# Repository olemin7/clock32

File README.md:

# dependency
git clone git@github.com:olemin7/esp32_idf_libs.git libs
# Troubleshooting

* Program upload failure

    * Hardware connection is not correct: run `idf.py -p PORT monitor`, and reboot your board to see if there are any output logs.
    * The baud rate for downloading is too high: lower your baud rate in the `menuconfig` menu, and try again.

https://esp-idf-lib.readthedocs.io/en/latest/groups/bmp180.html

https://github.com/espressif/esp-iot-solution

# esp32c3_supermini
    Pin     | ADC | func |
GPIO_NUM_0  | A0  |      |photoresistor
GPIO_NUM_1  | A1  |      |
GPIO_NUM_2  | A2  |      |
GPIO_NUM_3  | A3  |      |
GPIO_NUM_4  | A4  | SCK  | max7219 CLK
3V3
GND
5V
-------------------------------------
GPIO_NUM_5  | A5  | MISO | max7219 CS
GPIO_NUM_6  |     | MOSI | max7219 DIN
GPIO_NUM_7  |     | SS   | 
GPIO_NUM_8  |     | SDA  | LED           |HTU2x SDA
GPIO_NUM_9  |     | SDL  | BOOT_BUTTON   |HTU2x SDL
GPIO_NUM_10 |     |      |
GPIO_NUM_20 |     | RX   |
GPIO_NUM_21 |     | TX   |

# Display MAX7219 

https://github.com/DiegoPaezA/ESP32-freeRTOS/blob/master/i2c_scanner/main/i2c_scanner.c
https://github.com/espressif/esp-iot-solution/tree/dd15770d0f8c5fedea78809737f04b63d3765c83/examples/sensors/sensor_hub_monitor

# build CLI
. ~/esp/v5.5.1/esp-idf/export.sh
# path to esp32_idf_libs, relative to project root (used by main/Kconfig.projbuild)
# default: copy fetched by CMake FetchContent
export MY_ESP_LIBRARIES_PATH=/build/_deps/my_idf_libs-src
# to work on a local checkout of the libs instead (path is still appended to project root):
# export MY_ESP_LIBRARIES_LOCAL=1
idf.py set-target esp32c3
idf.py build
idf.py menuconfig
idf.py -p /dev/ttyACM0 flash

null in the env https://github.com/espressif/idf-eclipse-plugin/issues/535https://components.espressif.com/

Check the values in your sdkconfig for LOG_MAXIMUM_LEVEL. It defaults to matching LOG_DEFAULT_LEVEL which limits what values you can use by default.

# mqtt test
sudo apt-get install mosquitto mosquitto-clients

sudo vim /etc/mosquitto/mosquitto.conf 
add
  listener 1883 0.0.0.0
  allow_anonymous true

sudo ufw allow 1883

sudo /etc/init.d/mosquitto restart

mosquitto_sub -h nas.local -d -t advertisement
mosquitto_pub -h nas.local -d -t cmd -m "adv"

one terminal
mosquitto_sub -d -t hello/world
mosquitto_sub -d -t stat/weather -h central.local
Connect to another ssh session and run
mosquitto_pub -d -t hello/world -m "Hello from terminal window 2!"

sudo tail -f /var/log/mosquitto/mosquitto.log

mosquitto_sub -h nas.local -d -t '#'
https://github.com/nopnop2002/esp-idf-json/tree/master/json-basic-object

[rtc]
CONFIG_RTC_CLK_SRC ->External 32kHz crystal

[sntp]
Request interval to update time
CONFIG_TIMEZONE "GMT-2"
https://github.com/nayarsystems/posix_tz_db/blob/master/zones.csv
EET-2EEST,M3.5.0/3,M10.5.0/4

[button]
todo boot btn to go provision mode?

[termomenter]
https://www.lucadentella.it/en/2017/10/13/esp32-24-i2c-un-esempio-pratico-con-sensore-htu21d/
https://github.com/kimsniper/htu21d/tree/master/examples/esp32_implementation/main
si7021 (htu2x)

[esp-idf-lib]
https://esp-idf-lib.readthedocs.io/en/latest/index.html
git clone git@github.com:UncleRus/esp-idf-lib.git

[adc]
https://docs.espressif.com/projects/esp-idf/en/v4.4.8/esp32/api-reference/peripherals/adc.html
#photoresistor (GND ) -photoresistor- (A0) -resistor 10k- (+3.3)

https://esp32tutorials.com/esp32-esp-idf-max7219-dot-matrix-display

https://xantorohara.github.io/led-matrix-editor/#7e1818181c181800|7e060c3060663c00|3c66603860663c00|30307e3234383000|3c6660603e067e00|3c66663e06663c00|1818183030667e00|3c66663c66663c00|3c66607c66663c00|3c66666e76663c00

[json]
https://github.com/nopnop2002/esp-idf-json
# cmd list
export TARGET_MAC=64E833885558
export TARGET_MAC=64E833880880
export TARGET_MAC=64E83387D7D0
export TARGET_MAC=64E8338811DC
export TARGET_MAC=64E833882354
export MOSQUITO_ADDR=192.168.1.2
mosquitto_sub -d -t response/$TARGET_MAC -h $MOSQUITO_ADDR
mosquitto_sub -d -t devices/$TARGET_MAC/# -h $MOSQUITO_ADDR

mosquitto_pub -d -t cmd/$TARGET_MAC -h $MOSQUITO_ADDR -m '{"cmd":"help"}' 
mosquitto_pub -d -t cmd/$TARGET_MAC -h $MOSQUITO_ADDR -m '{"cmd":"version"}' 
mosquitto_pub -d -t cmd/$TARGET_MAC -h $MOSQUITO_ADDR -m '{"cmd":"svitlobot","payload":{"enabled":true,"interval_s":120}}' 
mosquitto_pub -d -t cmd/$TARGET_MAC -h $MOSQUITO_ADDR -m '{"cmd":"config"}' 

mosquitto_pub -d -t cmd/$TARGET_MAC -m '{"cmd":"ldr","payload":{"min":100,"max":3000}}' -h nas.local
mosquitto_pub -d -t cmd/$TARGET_MAC -m '{"cmd":"restart"}' -h $MOSQUITO_ADDR

mosquitto_pub -d -t cmd/$TARGET_MAC -m '{"cmd":"brightness","payload":{"points":[{"lighting":1530,"brightness":10}]}}' -h nas.local

mosquitto_pub -d -t cmd/$TARGET_MAC -h  $MOSQUITO_ADDR -m '{"cmd":"brightness","payload":{"points":[{"lighting":1530,"brightness":10}]}}' 

mosquitto_pub -d -t cmd/$TARGET_MAC -h $MOSQUITO_ADDR -m '{"cmd":"display"}'

{"cmd":"display","payload":{"segment_rotation":0,"segment_upsidedown":false,"mirrored":false}}

'{"cmd":"display","payload":{"segment_rotation":3,"segment_upsidedown":true,"mirrored":true}}
64E833885558 '{"cmd":"display","payload":{"segment_rotation":1,"segment_upsidedown":true,"mirrored":true}}'

'{"cmd":"timezone","payload":{"tz":"GMT-3"}}'
'{"cmd":"timezone","payload":{"tz":"EET-2EEST,M3.5.0/3,M10.5.0/4"}}'

[http command server]
url /cmd
smd the same as for mosqitoo
[IDF_PATH]

printenv IDF_PATH

export IDF_PATH="/home/oleksandrminenko/esp/v5.5.1/esp-idf"

[TODO]
custom data when provision

[test]
https://www.throwtheswitch.org/unity
idf.py -p /dev/ttyACM0 flash

[ota]
Two-slot OTA layout (partitions.csv): nvs/phy_init keep pre-OTA offsets, so the one-time USB migration
  flash preserves provisioning and settings; afterwards updates go over the air.
Each app slot is 0x1F0000 (~1.98 MB). Size budget guards: -Os, no TLS cert bundle (verification is off
  anyway), no IPv6. If the image outgrows the slot, the next lever is Bluedroid -> NimBLE (~200 KB).
flow:
  idf.py build
  cd build && python3 -m http.server 8070        # or copy clock32.bin to any LAN http server
  mosquitto_pub -t cmd/$TARGET_MAC -h $MOSQUITO_ADDR -m '{"cmd":"ota","payload":{"url":"http://<host-ip>:8070/clock32.bin"}}'
  mosquitto_pub -t cmd/$TARGET_MAC -h $MOSQUITO_ADDR -m '{"cmd":"ota"}'   # no payload -> status (slot, build date, state)
Rollback: CONFIG_BOOTLOADER_APP_ROLLBACK_ENABLE=y; the new image is confirmed (ota::mark_valid) only
  after Wi-Fi got an IP and the MQTT client was created - a crash-looping image rolls back on reset.
USB flash stays as recovery and for the one-time migration from the old single-factory layout.

[mink]
long press on boot btn ->reprovision

[svitlobot]
Keep-alive ping to SvitloBot (GET <SVITLOBOT_URL>?channel_key=<key>) every SVITLOBOT_INTERVAL_S while Wi-Fi is up.
cp main/svitlobot_secret.h.example main/svitlobot_secret.h   # git-ignored, set the real channel key
empty key / missing file -> feature disabled (warning in log)
menuconfig: App Configuration -> SvitloBot (URL, interval 65..600 s, default 120; timeout 3..30 s, default 8; startup jitter 0..600 s, default 30)
Runtime switch + period (NVS, survive reboot/OTA, part of {"cmd":"config"}), OFF BY DEFAULT
  (SVITLOBOT_DEFAULT_ENABLED=n, the menuconfig interval is only the default):
  mosquitto_pub -t cmd/$TARGET_MAC -h $MOSQUITO_ADDR -m '{"cmd":"svitlobot","payload":{"enabled":true}}'
  mosquitto_pub -t cmd/$TARGET_MAC -h $MOSQUITO_ADDR -m '{"cmd":"svitlobot","payload":{"interval_s":90}}'
  mosquitto_pub -t cmd/$TARGET_MAC -h $MOSQUITO_ADDR -m '{"cmd":"svitlobot"}'   # -> {"enabled":true, "interval_s":90}
  Enable on EXACTLY ONE clock per channel: the fleet must stay at <= 2 requests/min (429 replies count).
  interval_s outside 65..600 is rejected (reply keeps the old value); a change applies at once
  (the next ping is one new period after the change); disabling stops pings without a reboot.
  Rollout: a clock stops pinging as soon as it gets this firmware - update and enable the pinger first.
Several clocks in one location intentionally share the same channel key: if at least one of them gets
  through, the location is known to have power.
The API records one ping per minute PER CHANNEL and answers HTTP 429 "That's too fast bro, once request
  per minute please :)" to the rest. With a shared key that is normal and harmless - a sibling device
  already reported for us - so 429 is logged at info level and treated as success, NOT retried
  (retrying would only earn another 429).
Interval bounds: above 60 s because of the rate limit (static_assert enforces >= 65 s), and far enough
  below 240 s because the server posts " Світло зникло " after 4 minutes without an accepted ping.
  An interval of 55 s used to make every ping of a single device race the limiter, which is what
  produced the multi-minute holes - and the false blackout reports - in the channel history.
transport error / other HTTP status -> retry in 5 s, then 10 s, then every 20 s until it succeeds, so a
  transport failure never costs a whole interval and a missed cycle means a real outage
first ping after boot is delayed by a random 0..SVITLOBOT_STARTUP_JITTER_S (0 = off) so that devices
  coming back together after a blackout do not all hit the API in the same second; periodic pings are not jittered
  (jitter must be <= interval, enforced by a static_assert)
reconnect -> pings immediately (the sleep is aborted), a missed GOT_IP event is recovered from the netif state
NOTE: the timeout is per socket operation, not for the whole request; DNS resolution is not covered by it at all.
NOTE: CONFIG_ESP_TLS_INSECURE + CONFIG_ESP_TLS_SKIP_SERVER_CERT_VERIFY are enabled,
      server cert verification is off for ALL TLS connections in the firmware.

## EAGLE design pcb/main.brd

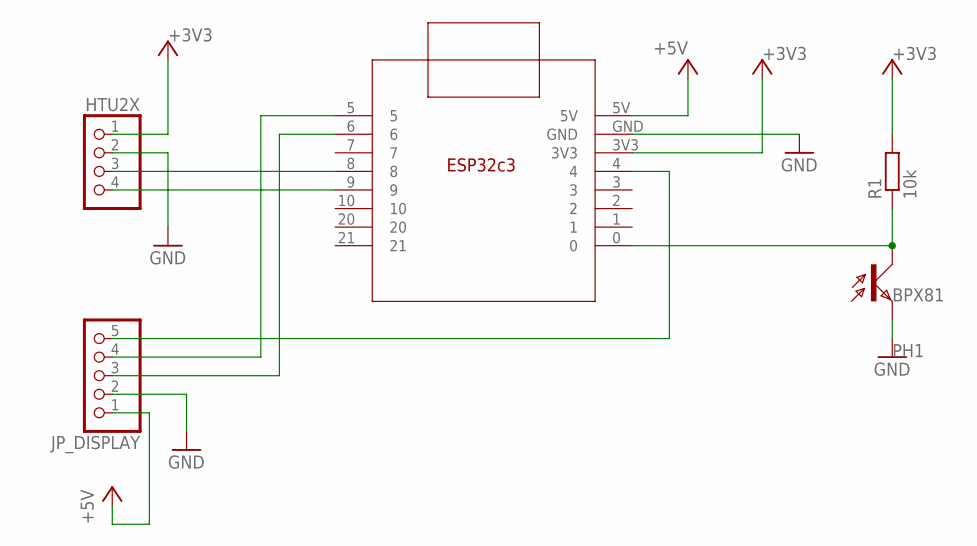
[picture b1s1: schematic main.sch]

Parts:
HTU2X: PINHD-1X4; 1X04
JP_DISPLAY: PINHD-1X5; 1X05
PH1: BPX81
R1: 10k; R0805
U$2: ESP32C3SMD; ESP32C3_SMD

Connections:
+3V3: HTU2X.1, R1.2, U$2.3V3
+5V: JP_DISPLAY.1, U$2.5V
GND: HTU2X.2, JP_DISPLAY.2, PH1.E, U$2.GND
unnamed: JP_DISPLAY.3, U$2.6
unnamed: PH1.C, R1.1, U$2.0
unnamed: HTU2X.3, U$2.8
unnamed: HTU2X.4, U$2.9
unnamed: JP_DISPLAY.4, U$2.5
unnamed: JP_DISPLAY.5, U$2.4

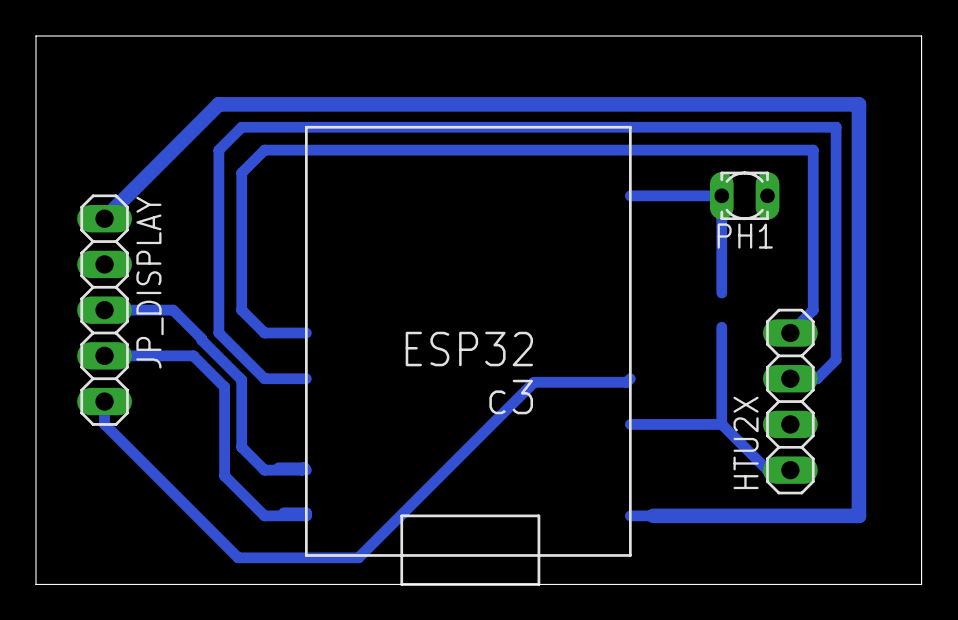
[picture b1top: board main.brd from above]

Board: 2 copper layers, 49.2 x 30.5 mm, 5 parts (1 on the bottom side), 9 nets.

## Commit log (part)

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2025-01-10 initial
2025-01-11 snpt draft
2025-01-12 snpd
2025-01-18 presistor
2025-01-19 add el
2025-01-20 el sensors
2025-01-20 layout
2025-01-20 beg display
2025-01-21 display transformation
2025-01-21 layesr
2025-01-22 clock
2025-01-24 mqtt
2025-01-29 prov
2025-02-01 pers
2025-02-16 adv msg upd
2025-02-20 + CONFIG_SENSORS_KA_PERIOD_S
2025-03-11 refacor
2025-03-11 unit_tests
2025-03-13 unit tests
2025-03-14 impl brignest
2025-03-14 stabilisation
2025-03-22 add utils
2025-03-22 puller rssi
2025-03-22 kconfig
2025-03-25 time widhth
2025-03-26 upd sntp, tz
2025-04-03 fix double free mqtt
2025-06-03 atart on http api
2025-06-04 http server
2025-06-04 add mqtt cmd
2025-06-06 upd mqtt adress
2025-11-25 ver up
2025-11-25 move to lib usage
2025-11-27 mqtt as component
2026-03-07 use local lib
2026-03-07 move to managed library
2026-03-08 add proto config command
2026-06-23 upd timezone
